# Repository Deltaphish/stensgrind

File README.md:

# Stensgrind
## Split keyboard with Corne layout, WIP

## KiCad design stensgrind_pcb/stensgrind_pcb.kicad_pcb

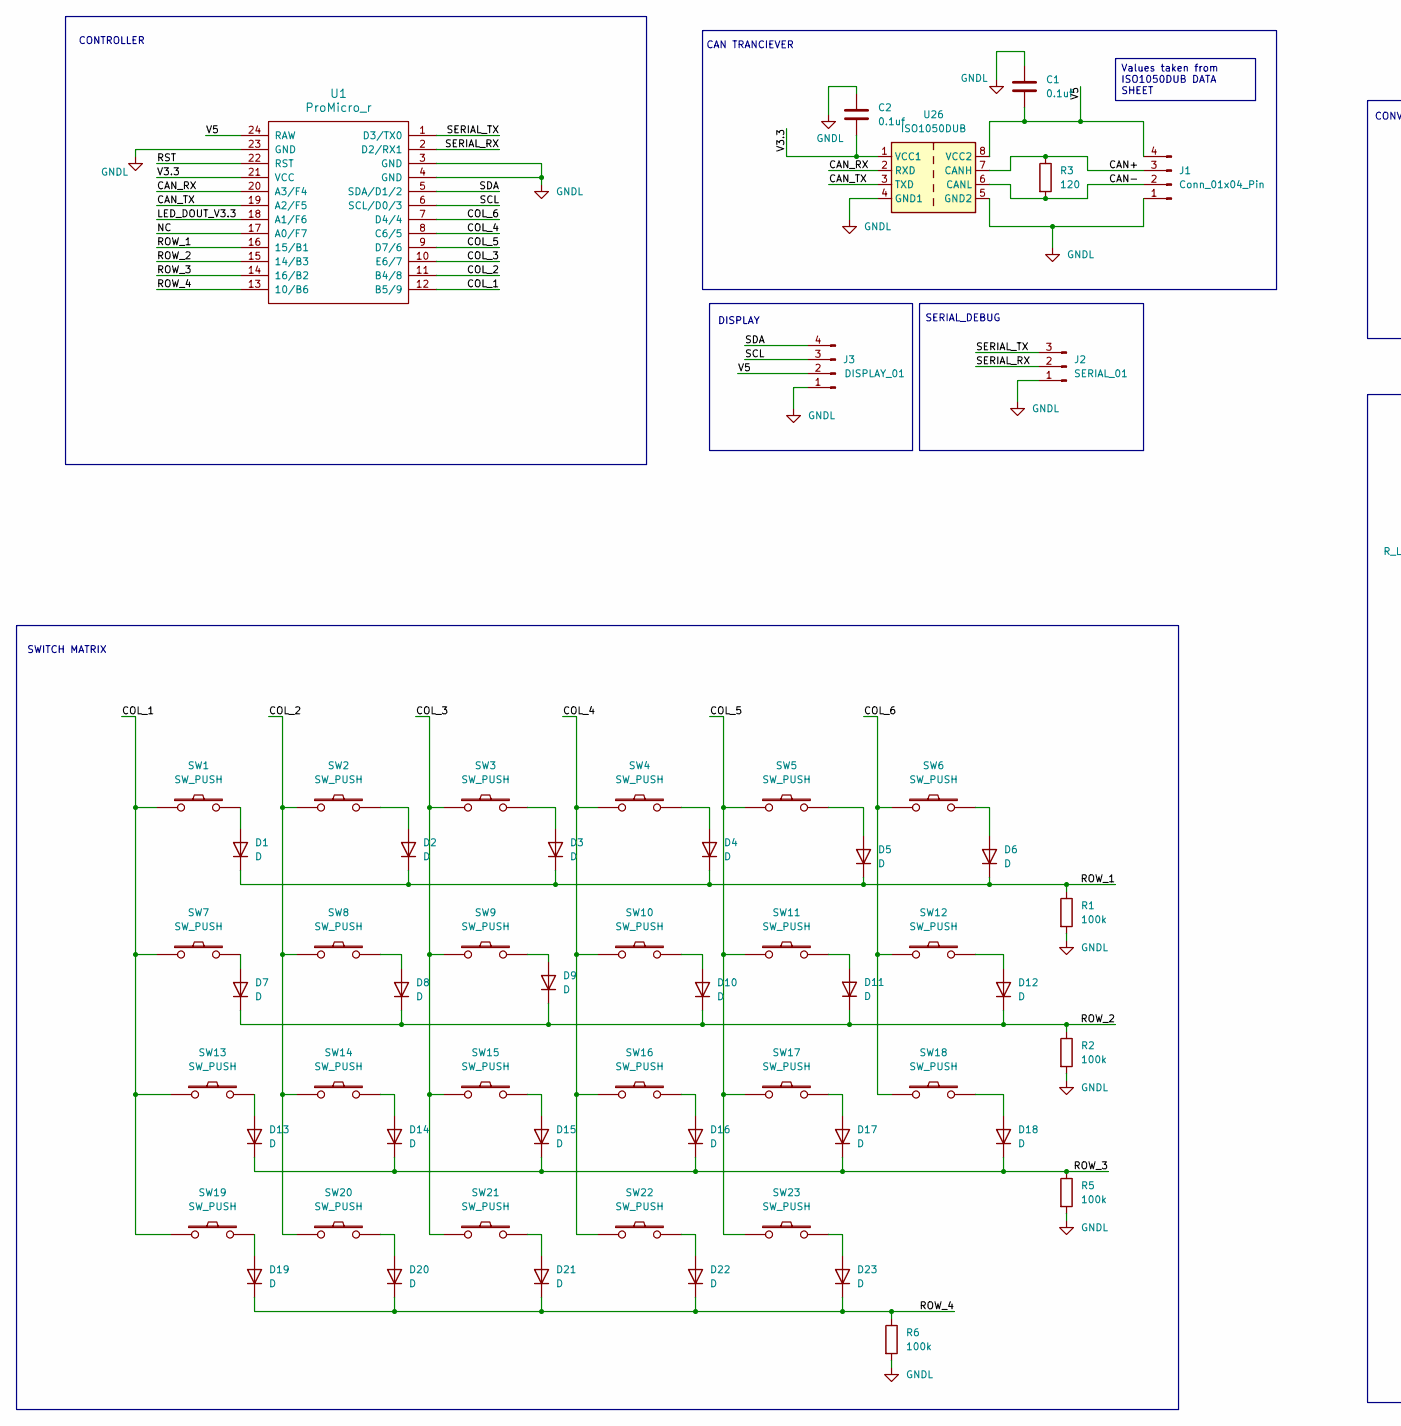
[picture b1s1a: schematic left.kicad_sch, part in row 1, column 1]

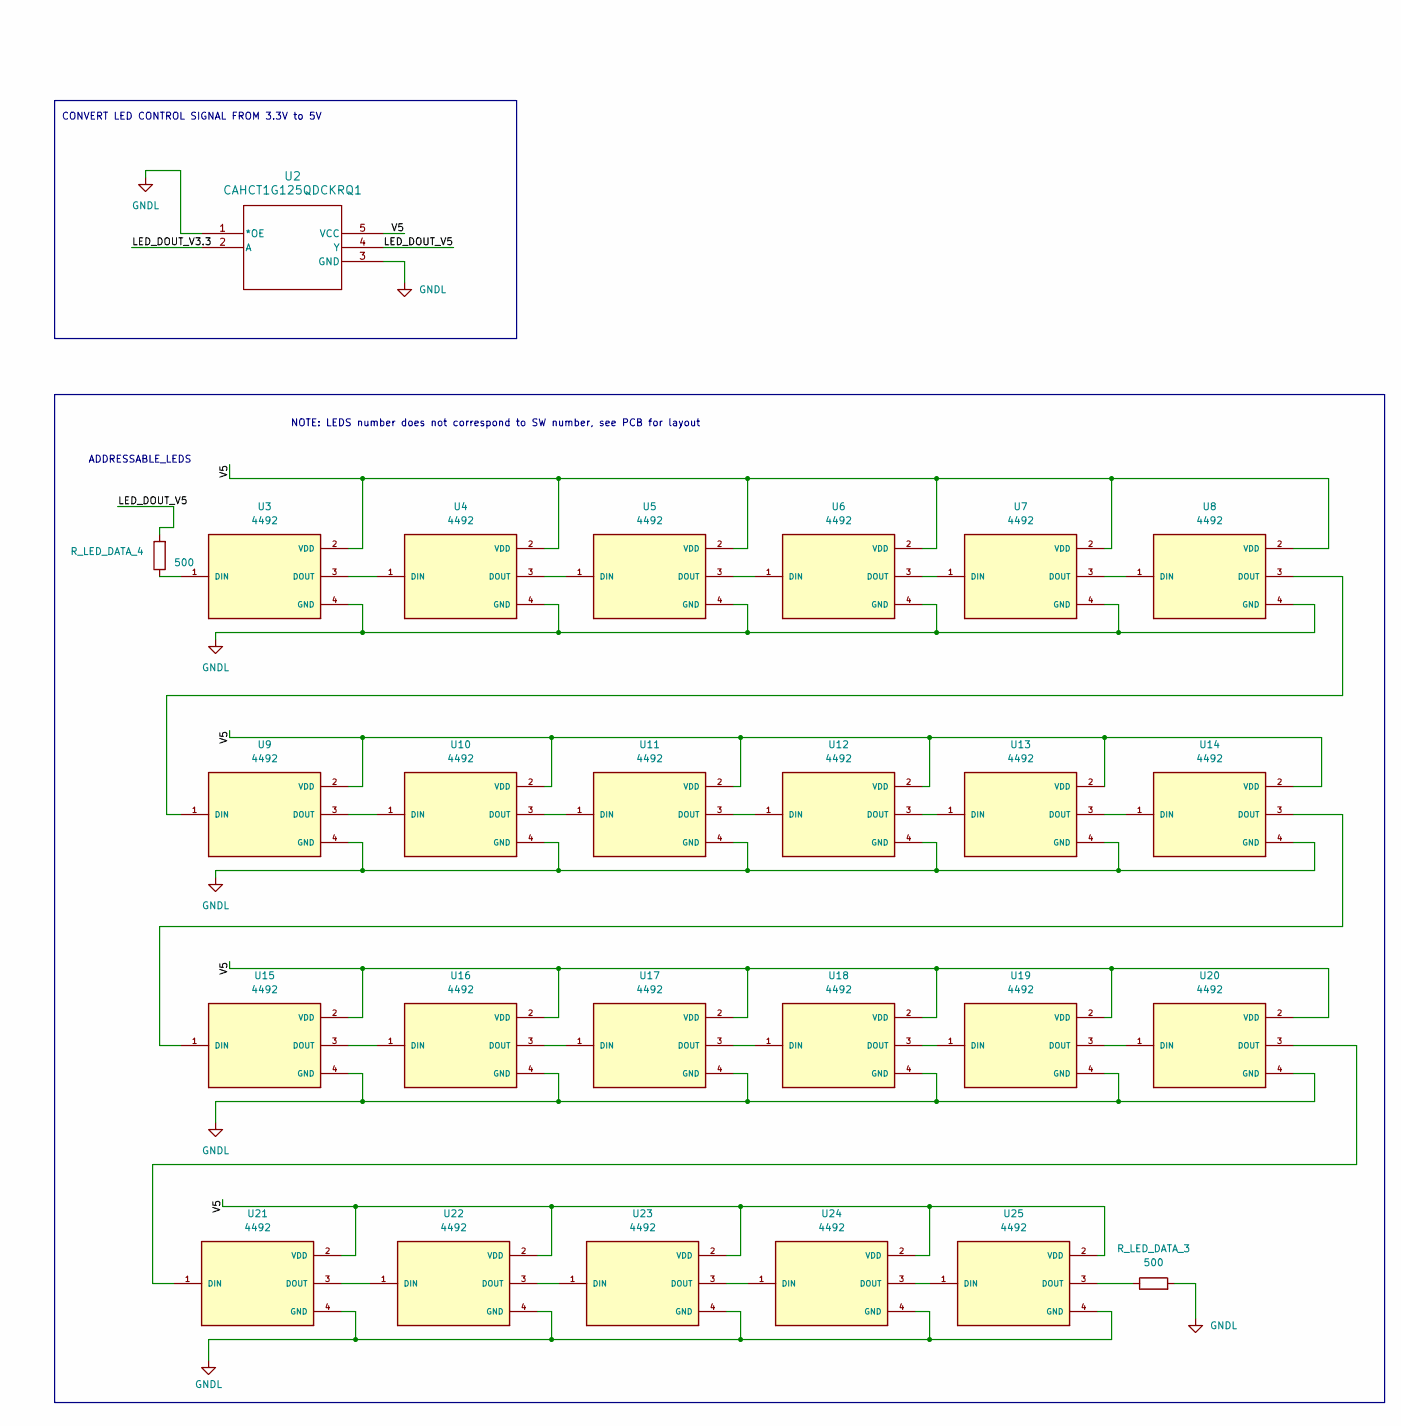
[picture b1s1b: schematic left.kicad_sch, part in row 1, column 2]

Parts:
C1, C2: 0.1uf; C_0805_2012Metric_Pad1.18x1.45mm_HandSolder
D1, D2, D3, D4, D5, D6, D7, D8, D9, D10, D11, D12, D13, D14, D15, D16, D17, D18, D19, D20, D21, D22, D23: D; D_DO-35_SOD27_P10.16mm_Horizontal
J1: Conn_01x04_Pin; PinSocket_1x04_P2.54mm_Vertical
J2: SERIAL_01; PinSocket_1x03_P2.54mm_Vertical
J3: DISPLAY_01; PinSocket_1x04_P2.54mm_Vertical
R1, R2, R5, R6: 100k; R_1206_3216Metric_Pad1.30x1.75mm_HandSolder
R3: 120; R_1206_3216Metric_Pad1.30x1.75mm_HandSolder
R_LED_DATA_3, R_LED_DATA_4: 500; R_1206_3216Metric_Pad1.30x1.75mm_HandSolder
SW1, SW2, SW3, SW4, SW5, SW6, SW7, SW8, SW9, SW10, SW11, SW12, SW13, SW14, SW15, SW16, SW17, SW18, SW19, SW20, SW21, SW22, SW23: SW_PUSH; keyswitch_cherrymx_hotswap_1u
U1: ProMicro_r; ProMicro
U2: CAHCT1G125QDCKRQ1; DCK5
U3, U4, U5, U6, U7, U8, U9, U10, U11, U12, U13, U14, U15, U16, U17, U18, U19, U20, U21, U22, U23, U24, U25: 4492; LED_4492; PARTREV 14/10/19
U26: ISO1050DUB; SOP-8_6.62x9.15mm_P2.54mm

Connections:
/LEFT_SIDE/CAN+: J1.3, R3.1, U26.7 (CANH)
/LEFT_SIDE/CAN-: J1.2, R3.2, U26.6 (CANL)
/LEFT_SIDE/CAN_RX: U1.20 (A3/F4), U26.2 (RXD)
/LEFT_SIDE/CAN_TX: U1.19 (A2/F5), U26.3 (TXD)
/LEFT_SIDE/COL_1: SW1.1, SW7.1, SW13.1, SW19.1, U1.12 (B5/9)
/LEFT_SIDE/COL_2: SW2.1, SW8.1, SW14.1, SW20.1, U1.11 (B4/8)
/LEFT_SIDE/COL_3: SW3.1, SW9.1, SW15.1, SW21.1, U1.10 (E6/7)
/LEFT_SIDE/COL_4: SW4.1, SW10.1, SW16.1, SW22.1, U1.8 (C6/5)
/LEFT_SIDE/COL_5: SW5.1, SW11.1, SW17.1, SW23.1, U1.9 (D7/6)
/LEFT_SIDE/COL_6: SW6.1, SW12.1, SW18.1, U1.7 (D4/4)
/LEFT_SIDE/LED_DOUT_V3.3: U1.18 (A1/F6), U2.2 (A)
/LEFT_SIDE/LED_DOUT_V5: R_LED_DATA_4.2, U2.4 (Y)
/LEFT_SIDE/NC: U1.17 (A0/F7)
/LEFT_SIDE/ROW_1: D1.1 (K), D2.1 (K), D3.1 (K), D4.1 (K), D5.1 (K), D6.1 (K), R1.1, U1.16 (15/B1)
/LEFT_SIDE/ROW_2: D7.1 (K), D8.1 (K), D9.1 (K), D10.1 (K), D11.1 (K), D12.1 (K), R2.1, U1.15 (14/B3)
/LEFT_SIDE/ROW_3: D13.1 (K), D14.1 (K), D15.1 (K), D16.1 (K), D17.1 (K), D18.1 (K), R5.1, U1.14 (16/B2)
/LEFT_SIDE/ROW_4: D19.1 (K), D20.1 (K), D21.1 (K), D22.1 (K), D23.1 (K), R6.1, U1.13 (10/B6)
/LEFT_SIDE/RST: U1.22 (RST)
/LEFT_SIDE/SCL: J3.3, U1.6 (SCL/D0/3)
/LEFT_SIDE/SDA: J3.4, U1.5 (SDA/D1/2)
/LEFT_SIDE/SERIAL_RX: J2.2, U1.2 (D2/RX1)
/LEFT_SIDE/SERIAL_TX: J2.3, U1.1 (D3/TX0)
/LEFT_SIDE/V3.3: C2.2, U1.21 (VCC), U26.1 (VCC1)
/LEFT_SIDE/V5: C1.2, J1.4, J3.2, U1.24 (RAW), U2.5 (VCC), U3.2 (VDD), U4.2 (VDD), U5.2 (VDD), U6.2 (VDD), U7.2 (VDD), U8.2 (VDD), U9.2 (VDD), U10.2 (VDD), U11.2 (VDD), U12.2 (VDD), U13.2 (VDD), U14.2 (VDD), U15.2 (VDD), U16.2 (VDD), U17.2 (VDD), U18.2 (VDD), U19.2 (VDD), U20.2 (VDD), U21.2 (VDD), U22.2 (VDD), U23.2 (VDD), U24.2 (VDD), U25.2 (VDD), U26.8 (VCC2)
GNDL: C1.1, C2.1, J1.1, J2.1, J3.1, R1.2, R2.2, R5.2, R6.2, R_LED_DATA_3.2, U1.3 (GND), U1.4 (GND), U1.23 (GND), U2.1 (*OE), U2.3 (GND), U3.4 (GND), U4.4 (GND), U5.4 (GND), U6.4 (GND), U7.4 (GND), U8.4 (GND), U9.4 (GND), U10.4 (GND), U11.4 (GND), U12.4 (GND), U13.4 (GND), U14.4 (GND), U15.4 (GND), U16.4 (GND), U17.4 (GND), U18.4 (GND), U19.4 (GND), U20.4 (GND), U21.4 (GND), U22.4 (GND), U23.4 (GND), U24.4 (GND), U25.4 (GND), U26.4 (GND1), U26.5 (GND2)
unnamed: D1.2 (A), SW1.2
unnamed: D2.2 (A), SW2.2
unnamed: D3.2 (A), SW3.2
unnamed: D4.2 (A), SW4.2
unnamed: D5.2 (A), SW5.2
unnamed: D6.2 (A), SW6.2
unnamed: D7.2 (A), SW7.2
unnamed: D8.2 (A), SW8.2
unnamed: D9.2 (A), SW9.2
unnamed: D10.2 (A), SW10.2
unnamed: D11.2 (A), SW11.2
unnamed: D12.2 (A), SW12.2
unnamed: D13.2 (A), SW13.2
unnamed: D14.2 (A), SW14.2
unnamed: D15.2 (A), SW15.2
unnamed: D16.2 (A), SW16.2
unnamed: D17.2 (A), SW17.2
unnamed: D18.2 (A), SW18.2
unnamed: D19.2 (A), SW19.2
unnamed: D20.2 (A), SW20.2
unnamed: D21.2 (A), SW21.2
unnamed: D22.2 (A), SW22.2
unnamed: D23.2 (A), SW23.2
unnamed: R_LED_DATA_4.1, U3.1 (DIN)
unnamed: U3.3 (DOUT), U4.1 (DIN)
unnamed: U4.3 (DOUT), U5.1 (DIN)
unnamed: U5.3 (DOUT), U6.1 (DIN)
unnamed: U6.3 (DOUT), U7.1 (DIN)
unnamed: U7.3 (DOUT), U8.1 (DIN)
unnamed: U8.3 (DOUT), U9.1 (DIN)
unnamed: U9.3 (DOUT), U10.1 (DIN)
unnamed: U10.3 (DOUT), U11.1 (DIN)
unnamed: U11.3 (DOUT), U12.1 (DIN)
unnamed: U12.3 (DOUT), U13.1 (DIN)
unnamed: U13.3 (DOUT), U14.1 (DIN)
unnamed: U14.3 (DOUT), U15.1 (DIN)
unnamed: U15.3 (DOUT), U16.1 (DIN)
unnamed: U16.3 (DOUT), U17.1 (DIN)
unnamed: U17.3 (DOUT), U18.1 (DIN)
unnamed: U18.3 (DOUT), U19.1 (DIN)
unnamed: U19.3 (DOUT), U20.1 (DIN)
unnamed: U20.3 (DOUT), U21.1 (DIN)
unnamed: U21.3 (DOUT), U22.1 (DIN)
unnamed: U22.3 (DOUT), U23.1 (DIN)
unnamed: U23.3 (DOUT), U24.1 (DIN)
unnamed: U24.3 (DOUT), U25.1 (DIN)
unnamed: R_LED_DATA_3.1, U25.3 (DOUT)

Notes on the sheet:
SWITCH MATRIX
DISPLAY
CAN TRANCIEVER
SERIAL_DEBUG
CONTROLLER
CONVERT LED CONTROL SIGNAL FROM 3.3V to 5V
ADDRESSABLE_LEDS
NOTE: LEDS number does not correspond to SW number, see PCB for layout
Values taken from ISO1050DUB DATA SHEET

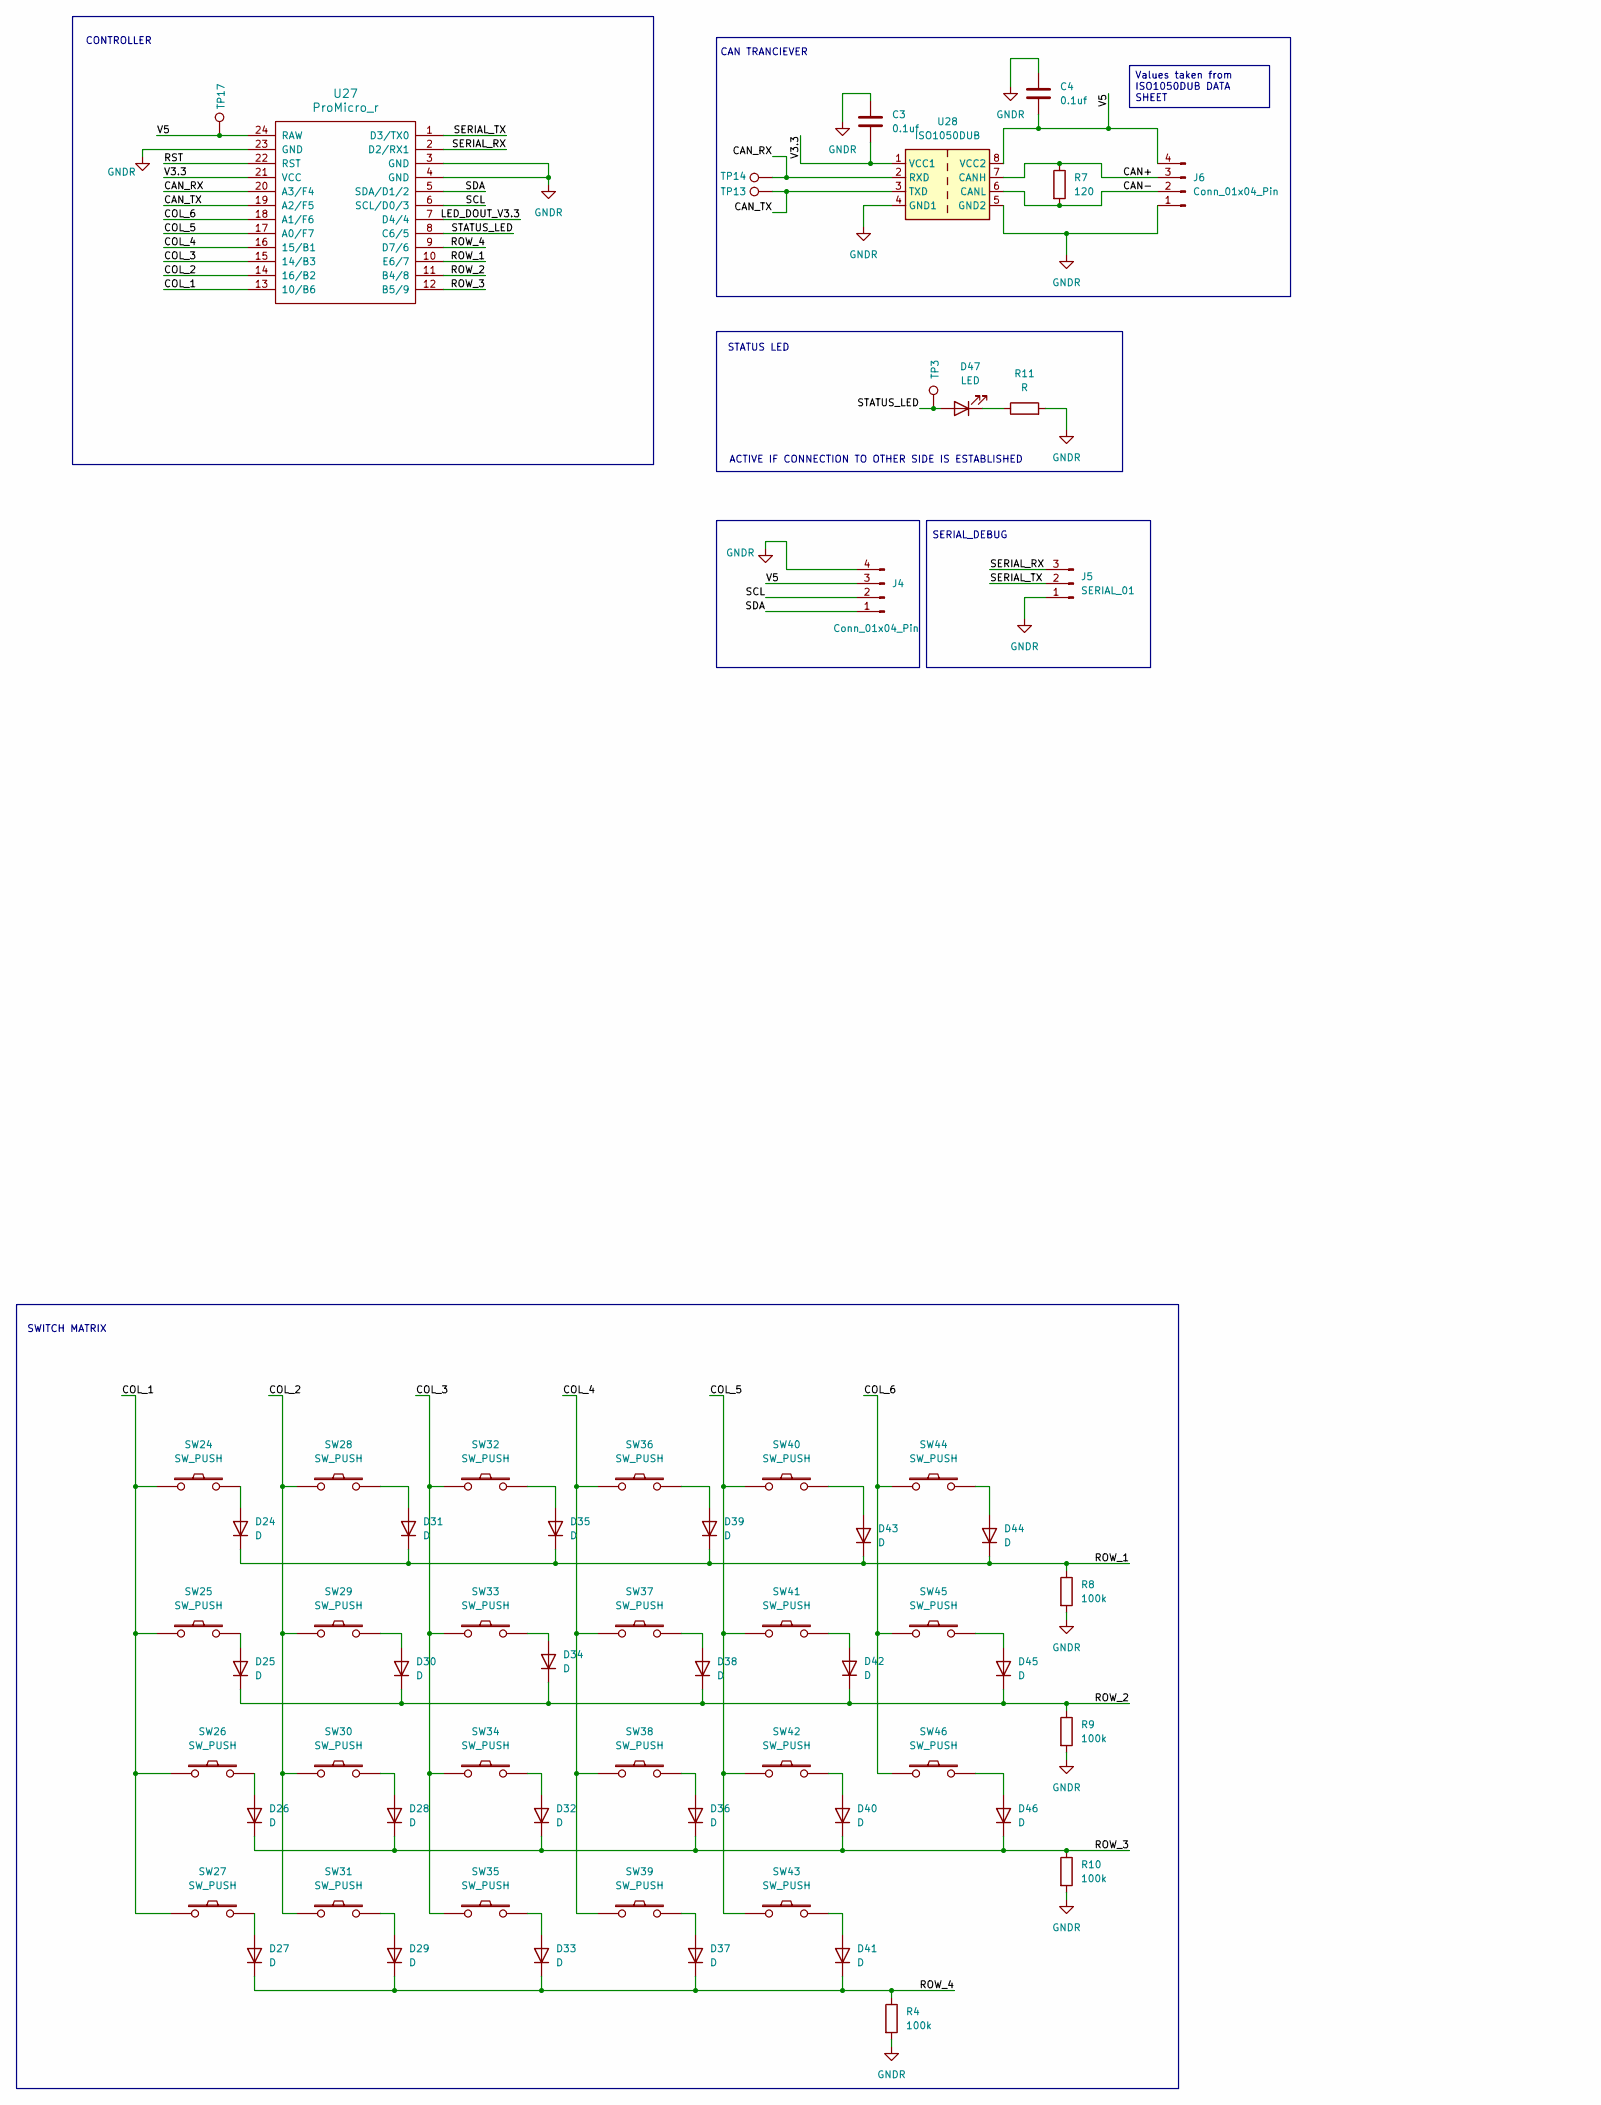
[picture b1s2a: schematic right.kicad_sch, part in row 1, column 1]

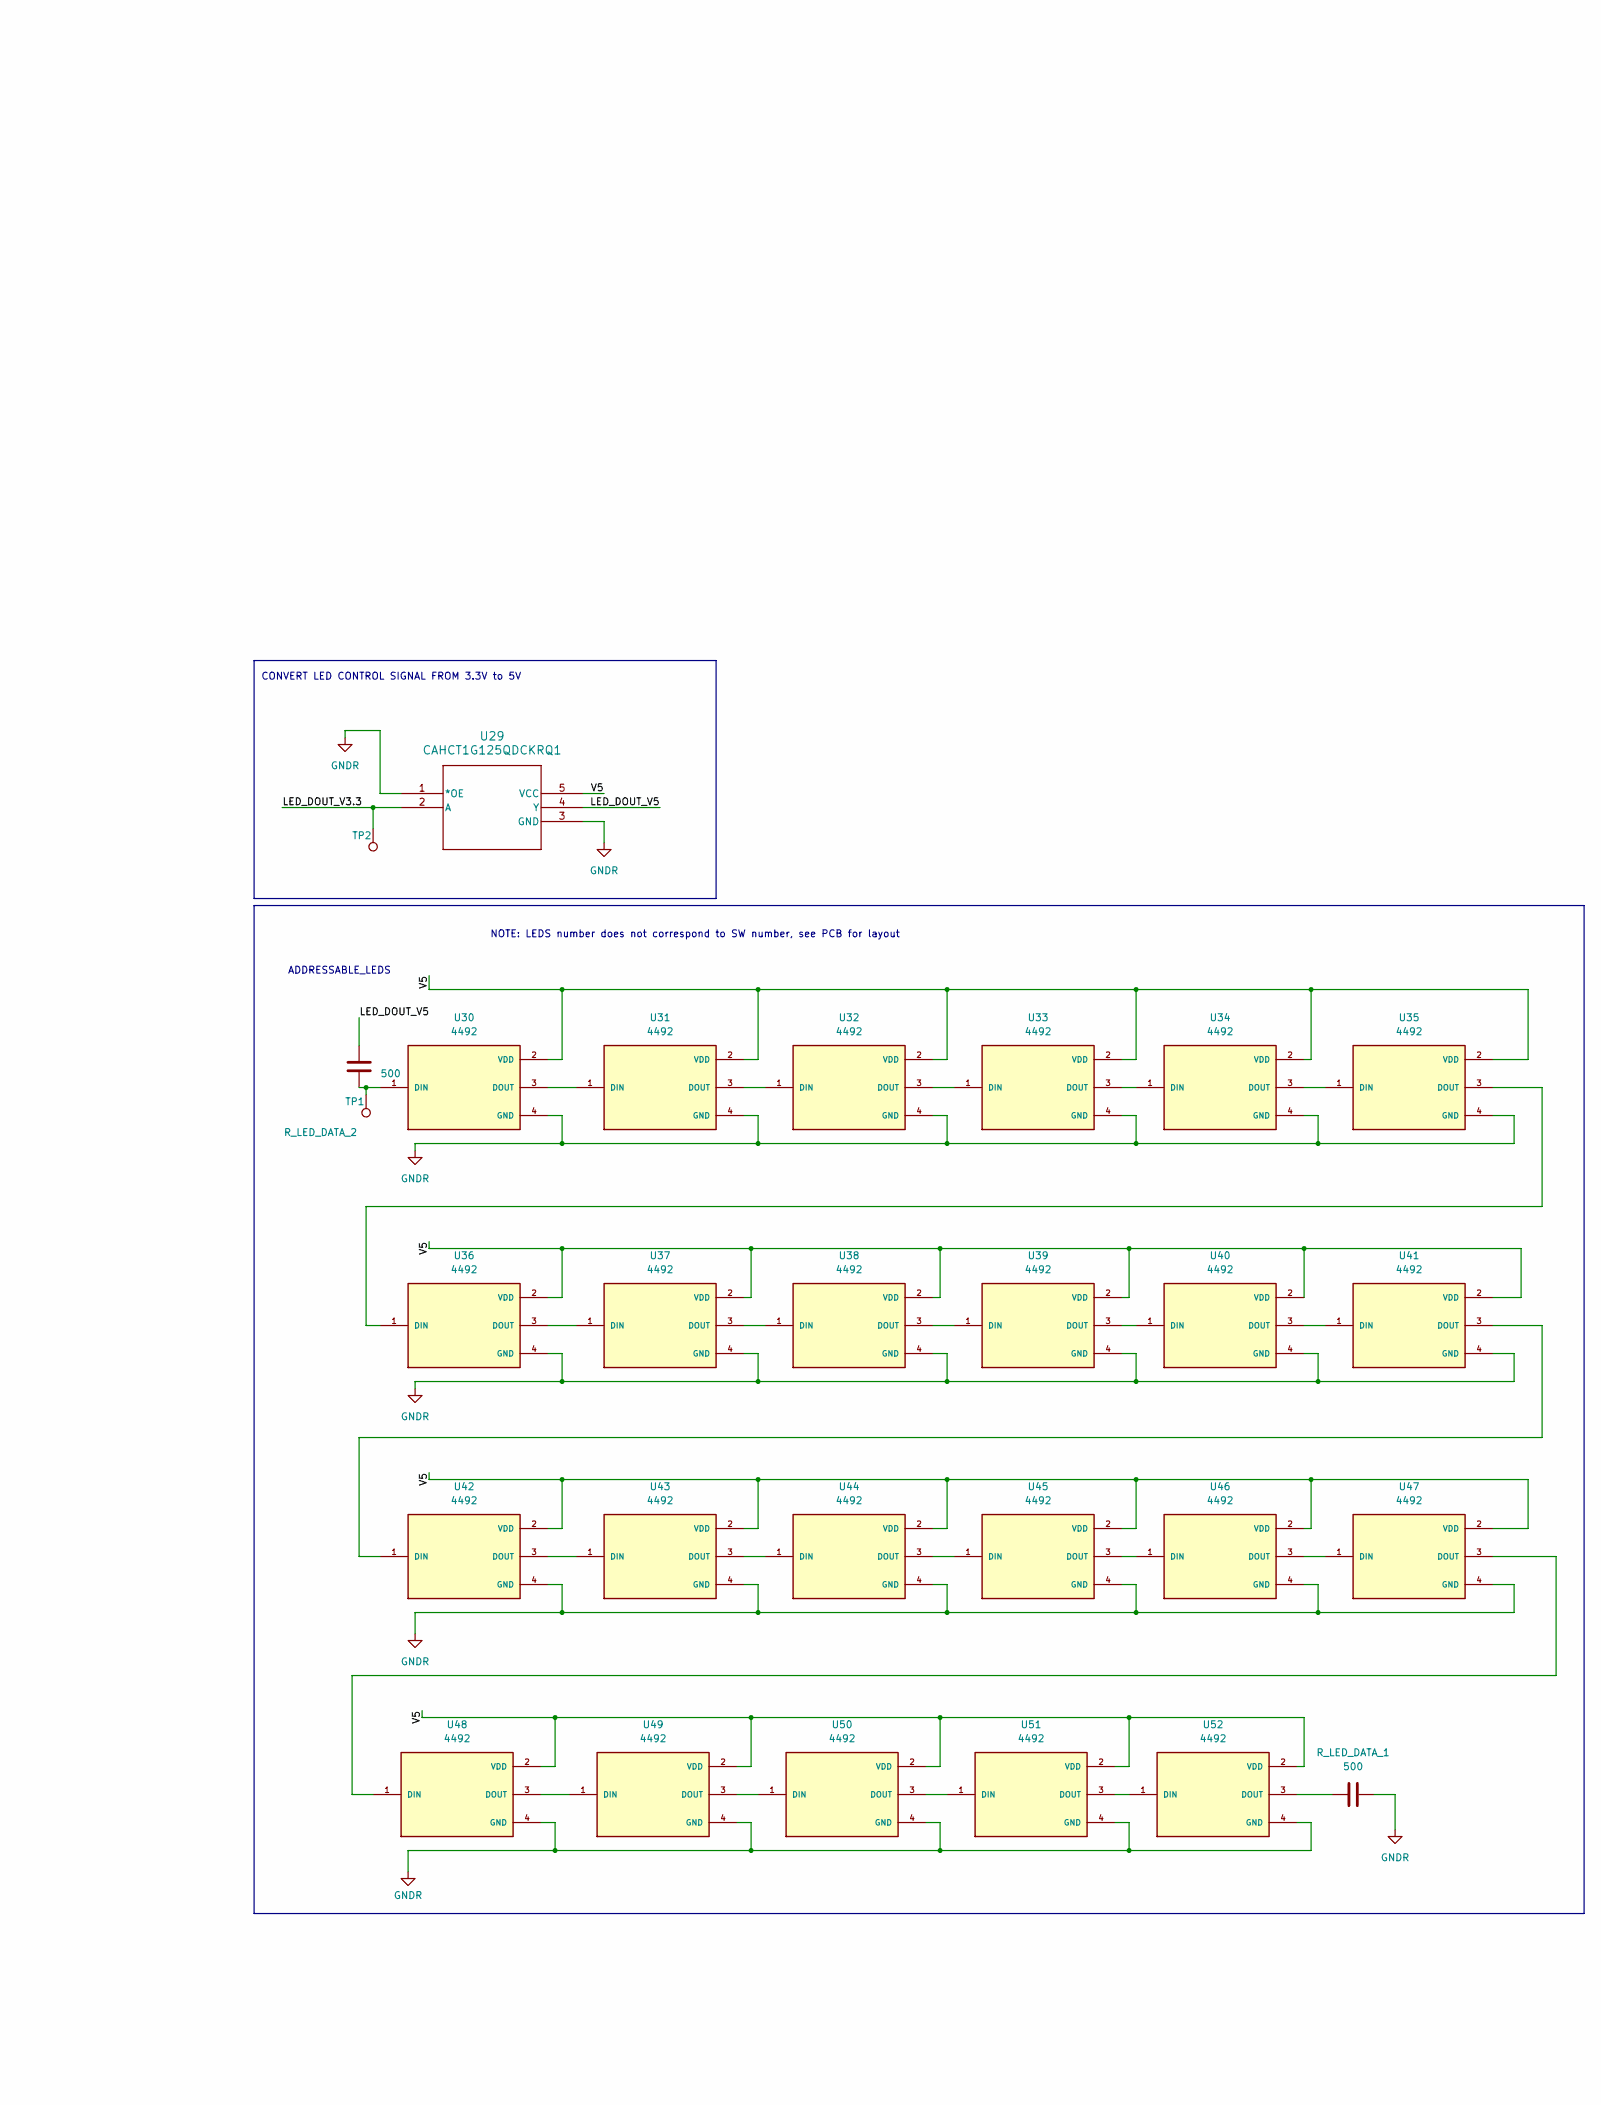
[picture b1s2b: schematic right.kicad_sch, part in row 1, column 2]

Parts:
C3, C4: 0.1uf; C_0805_2012Metric_Pad1.18x1.45mm_HandSolder
D24, D25, D26, D27, D28, D29, D30, D31, D32, D33, D34, D35, D36, D37, D38, D39, D40, D41, D42, D43, D44, D45, D46: D; D_DO-35_SOD27_P10.16mm_Horizontal
D47: LED; LED_1206_3216Metric
J4, J6: Conn_01x04_Pin; PinSocket_1x04_P2.54mm_Vertical
J5: SERIAL_01; PinSocket_1x03_P2.54mm_Vertical
R4, R8, R9, R10: 100k; R_1206_3216Metric_Pad1.30x1.75mm_HandSolder
R7: 120; R_1206_3216Metric_Pad1.30x1.75mm_HandSolder
R11: R; R_1206_3216Metric_Pad1.30x1.75mm_HandSolder
R_LED_DATA_1, R_LED_DATA_2: 500; R_1206_3216Metric_Pad1.30x1.75mm_HandSolder
SW24, SW25, SW26, SW27, SW28, SW29, SW30, SW31, SW32, SW33, SW34, SW35, SW36, SW37, SW38, SW39, SW40, SW41, SW42, SW43, SW44, SW45, SW46: SW_PUSH; keyswitch_cherrymx_hotswap_1u
TP1, TP2, TP3, TP13, TP14, TP17: 0.5mm; TestPoint-0.5mm
U27: ProMicro_r; ProMicro
U28: ISO1050DUB; SOP-8_6.62x9.15mm_P2.54mm
U29: CAHCT1G125QDCKRQ1; DCK5
U30, U31, U32, U33, U34, U35, U36, U37, U38, U39, U40, U41, U42, U43, U44, U45, U46, U47, U48, U49, U50, U51, U52: 4492; LED_4492; PARTREV 14/10/19

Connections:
/RIGHT_SIDE/CAN+: J6.3, R7.1, U28.7 (CANH)
/RIGHT_SIDE/CAN-: J6.2, R7.2, U28.6 (CANL)
/RIGHT_SIDE/CAN_RX: TP14.1, U27.20 (A3/F4), U28.2 (RXD)
/RIGHT_SIDE/CAN_TX: TP13.1, U27.19 (A2/F5), U28.3 (TXD)
/RIGHT_SIDE/COL_1: SW24.1, SW25.1, SW26.1, SW27.1, U27.13 (10/B6)
/RIGHT_SIDE/COL_2: SW28.1, SW29.1, SW30.1, SW31.1, U27.14 (16/B2)
/RIGHT_SIDE/COL_3: SW32.1, SW33.1, SW34.1, SW35.1, U27.15 (14/B3)
/RIGHT_SIDE/COL_4: SW36.1, SW37.1, SW38.1, SW39.1, U27.16 (15/B1)
/RIGHT_SIDE/COL_5: SW40.1, SW41.1, SW42.1, SW43.1, U27.17 (A0/F7)
/RIGHT_SIDE/COL_6: SW44.1, SW45.1, SW46.1, U27.18 (A1/F6)
/RIGHT_SIDE/LED_DOUT_V3.3: TP2.1, U27.7 (D4/4), U29.2 (A)
/RIGHT_SIDE/LED_DOUT_V5: R_LED_DATA_2.2, U29.4 (Y)
/RIGHT_SIDE/ROW_1: D24.1 (K), D31.1 (K), D35.1 (K), D39.1 (K), D43.1 (K), D44.1 (K), R8.1, U27.10 (E6/7)
/RIGHT_SIDE/ROW_2: D25.1 (K), D30.1 (K), D34.1 (K), D38.1 (K), D42.1 (K), D45.1 (K), R9.1, U27.11 (B4/8)
/RIGHT_SIDE/ROW_3: D26.1 (K), D28.1 (K), D32.1 (K), D36.1 (K), D40.1 (K), D46.1 (K), R10.1, U27.12 (B5/9)
/RIGHT_SIDE/ROW_4: D27.1 (K), D29.1 (K), D33.1 (K), D37.1 (K), D41.1 (K), R4.1, U27.9 (D7/6)
/RIGHT_SIDE/RST: U27.22 (RST)
/RIGHT_SIDE/SCL: J4.2, U27.6 (SCL/D0/3)
/RIGHT_SIDE/SDA: J4.1, U27.5 (SDA/D1/2)
/RIGHT_SIDE/SERIAL_RX: J5.3, U27.2 (D2/RX1)
/RIGHT_SIDE/SERIAL_TX: J5.2, U27.1 (D3/TX0)
/RIGHT_SIDE/STATUS_LED: D47.2 (A), TP3.1, U27.8 (C6/5)
/RIGHT_SIDE/V3.3: C3.2, U27.21 (VCC), U28.1 (VCC1)
/RIGHT_SIDE/V5: C4.2, J4.3, J6.4, TP17.1, U27.24 (RAW), U28.8 (VCC2), U29.5 (VCC), U30.2 (VDD), U31.2 (VDD), U32.2 (VDD), U33.2 (VDD), U34.2 (VDD), U35.2 (VDD), U36.2 (VDD), U37.2 (VDD), U38.2 (VDD), U39.2 (VDD), U40.2 (VDD), U41.2 (VDD), U42.2 (VDD), U43.2 (VDD), U44.2 (VDD), U45.2 (VDD), U46.2 (VDD), U47.2 (VDD), U48.2 (VDD), U49.2 (VDD), U50.2 (VDD), U51.2 (VDD), U52.2 (VDD)
GNDR: C3.1, C4.1, J4.4, J5.1, J6.1, R4.2, R8.2, R9.2, R10.2, R11.2, R_LED_DATA_1.2, U27.3 (GND), U27.4 (GND), U27.23 (GND), U28.4 (GND1), U28.5 (GND2), U29.1 (*OE), U29.3 (GND), U30.4 (GND), U31.4 (GND), U32.4 (GND), U33.4 (GND), U34.4 (GND), U35.4 (GND), U36.4 (GND), U37.4 (GND), U38.4 (GND), U39.4 (GND), U40.4 (GND), U41.4 (GND), U42.4 (GND), U43.4 (GND), U44.4 (GND), U45.4 (GND), U46.4 (GND), U47.4 (GND), U48.4 (GND), U49.4 (GND), U50.4 (GND), U51.4 (GND), U52.4 (GND)
unnamed: D24.2 (A), SW24.2
unnamed: D25.2 (A), SW25.2
unnamed: D26.2 (A), SW26.2
unnamed: D27.2 (A), SW27.2
unnamed: D28.2 (A), SW30.2
unnamed: D29.2 (A), SW31.2
unnamed: D30.2 (A), SW29.2
unnamed: D31.2 (A), SW28.2
unnamed: D32.2 (A), SW34.2
unnamed: D33.2 (A), SW35.2
unnamed: D34.2 (A), SW33.2
unnamed: D35.2 (A), SW32.2
unnamed: D36.2 (A), SW38.2
unnamed: D37.2 (A), SW39.2
unnamed: D38.2 (A), SW37.2
unnamed: D39.2 (A), SW36.2
unnamed: D40.2 (A), SW42.2
unnamed: D41.2 (A), SW43.2
unnamed: D42.2 (A), SW41.2
unnamed: D43.2 (A), SW40.2
unnamed: D44.2 (A), SW44.2
unnamed: D45.2 (A), SW45.2
unnamed: D46.2 (A), SW46.2
unnamed: D47.1 (K), R11.1
unnamed: R_LED_DATA_2.1, TP1.1, U30.1 (DIN)
unnamed: U30.3 (DOUT), U31.1 (DIN)
unnamed: U31.3 (DOUT), U32.1 (DIN)
unnamed: U32.3 (DOUT), U33.1 (DIN)
unnamed: U33.3 (DOUT), U34.1 (DIN)
unnamed: U34.3 (DOUT), U35.1 (DIN)
unnamed: U35.3 (DOUT), U36.1 (DIN)
unnamed: U36.3 (DOUT), U37.1 (DIN)
unnamed: U37.3 (DOUT), U38.1 (DIN)
unnamed: U38.3 (DOUT), U39.1 (DIN)
unnamed: U39.3 (DOUT), U40.1 (DIN)
unnamed: U40.3 (DOUT), U41.1 (DIN)
unnamed: U41.3 (DOUT), U42.1 (DIN)
unnamed: U42.3 (DOUT), U43.1 (DIN)
unnamed: U43.3 (DOUT), U44.1 (DIN)
unnamed: U44.3 (DOUT), U45.1 (DIN)
unnamed: U45.3 (DOUT), U46.1 (DIN)
unnamed: U46.3 (DOUT), U47.1 (DIN)
unnamed: U47.3 (DOUT), U48.1 (DIN)
unnamed: U48.3 (DOUT), U49.1 (DIN)
unnamed: U49.3 (DOUT), U50.1 (DIN)
unnamed: U50.3 (DOUT), U51.1 (DIN)
unnamed: U51.3 (DOUT), U52.1 (DIN)
unnamed: R_LED_DATA_1.1, U52.3 (DOUT)

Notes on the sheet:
SERIAL_DEBUG
CONVERT LED CONTROL SIGNAL FROM 3.3V to 5V
CAN TRANCIEVER
SWITCH MATRIX
ADDRESSABLE_LEDS
CONTROLLER
STATUS LED
NOTE: LEDS number does not correspond to SW number, see PCB for layout
ACTIVE IF CONNECTION TO OTHER SIDE IS ESTABLISHED
Values taken from ISO1050DUB DATA SHEET

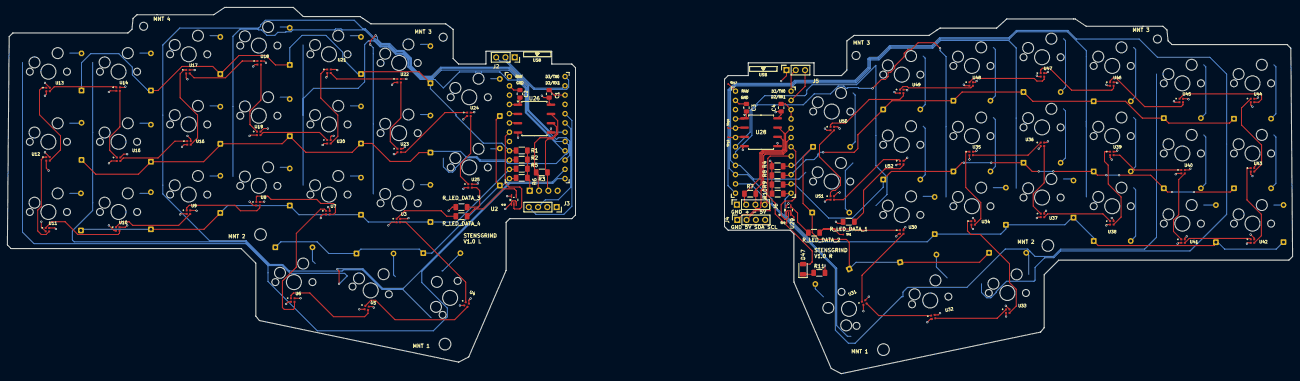
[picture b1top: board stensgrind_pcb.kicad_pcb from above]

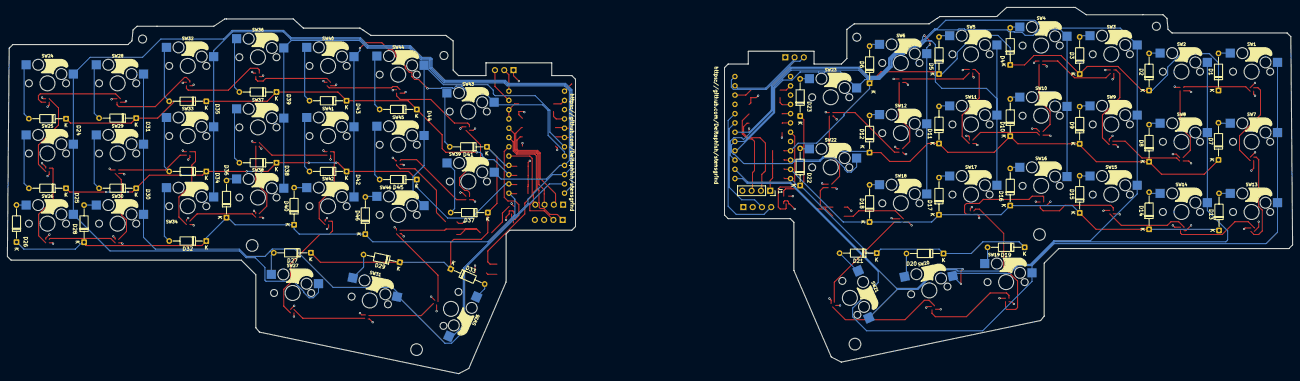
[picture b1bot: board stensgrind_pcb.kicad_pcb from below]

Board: 4 copper layers, 351.8 x 100.3 mm, 186 parts (93 on the bottom side), 142 nets.

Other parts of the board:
LEFT: Board
MNT 1, MNT 1#2, MNT 2, MNT 2#2: MountingHole_3.2mm_M3
MNT 3, MNT 3#2, MNT 3#3, MNT 4: MountingHole_2.2mm_M2
RIGHT: Board

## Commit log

2026-02-13 Add README
2026-02-13 Add MIT License for software
2026-02-13 Add CERN Open Hardware Licence
    This file contains the CERN Open Hardware Licence Version 2 - Permissive, outlining the terms for using, modifying, and distributing hardware designs.
2026-02-13 Fix project name spelling in README
2026-02-13 Keep switch name consistent
2026-02-13 Add link to project
2026-02-15 add right half
2026-02-15 ofcourse we are adding a touchpad
2026-02-20 Remove touchpad from main board, expose i2c instead
2026-02-21 finish up v1
2026-02-21 Update image
2026-02-21 fix i2c mapping
